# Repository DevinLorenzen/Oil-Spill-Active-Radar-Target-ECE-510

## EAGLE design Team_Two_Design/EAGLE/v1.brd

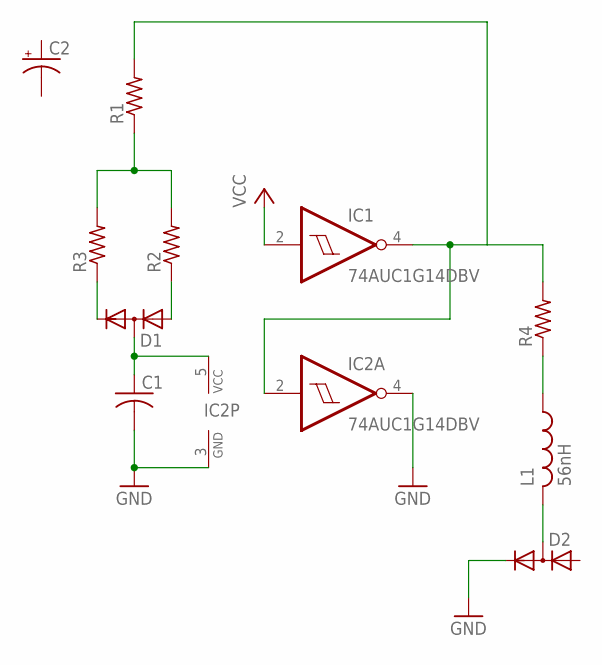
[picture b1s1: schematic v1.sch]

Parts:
C1: C-USC0402; C0402
C2: CPOL-USB; PANASONIC_B
D1, D2: DIODE_2CACA-SOT23; SOT23
IC1, IC2: 74AUC1G14DBV; SOT23-5
L1: 56nH; L2012C
R1, R2, R3, R4: R-US_R0805; R0805

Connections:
GND: C1.2, D2.2 (C), IC1.3 (GND), IC2.3, IC2.4 (O)
unnamed: D1.1 (A), R2.1
unnamed: D1.2 (C), R3.1
unnamed: IC1.4 (O), IC2.2 (I), R1.2, R4.2
unnamed: L1.1, R4.1
unnamed: R1.1, R2.2, R3.2
unnamed: C1.1, D1.3 (AC), IC2.5
unnamed: D2.3 (AC), L1.2
VCC: IC1.2 (I), IC1.5 (VCC)

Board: 2 copper layers, 11 parts (0 on the bottom side), 9 nets, no tracks yet.

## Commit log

2016-03-08 Got thresholding working
2016-03-08 Added example file
